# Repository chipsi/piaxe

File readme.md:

This Raspberry Pi mining HAT is based on the [BitAxe Ultra 1.3](https://github.com/skot/bitaxe
) (with BM1366) design.

Update: Miner is running stable 🥳

Changes to BitAxe Ultra
=======================

- powered by 12V and
- added TVS diode and fuses
- revised buck switching regulator circuit
- revised heatsink
- removed like DAC (only fixed 1.2V on PiAxe), current measurement, fan PWM controller, additional testpoints
- smallest components have 0805 size for easier manual assembly
- LM75 compatible temperature sensor under the heatsink

Installation
=============

- add to `/boot/config.txt`:
```
dtoverlay=pwm
```

- enable `serial` and `I2C` via `raspi-config`

If you want to use Influx and Grafana you need docker too:

```bash
$ curl -sSL https://get.docker.com | sh
```

Python:
```bash
# install pip3
$ sudo apt install python3-pip

# install libraries
$ for lib in pyserial rpi_hardware_pwm smbus influxdb-client pytz; do pip3 install $lib; done

# install i2c-tools
$ sudo apt install i2c-tools
```

Mining Client
=============

Stratum Mining Client:<br>
https://github.com/shufps/piaxe-miner

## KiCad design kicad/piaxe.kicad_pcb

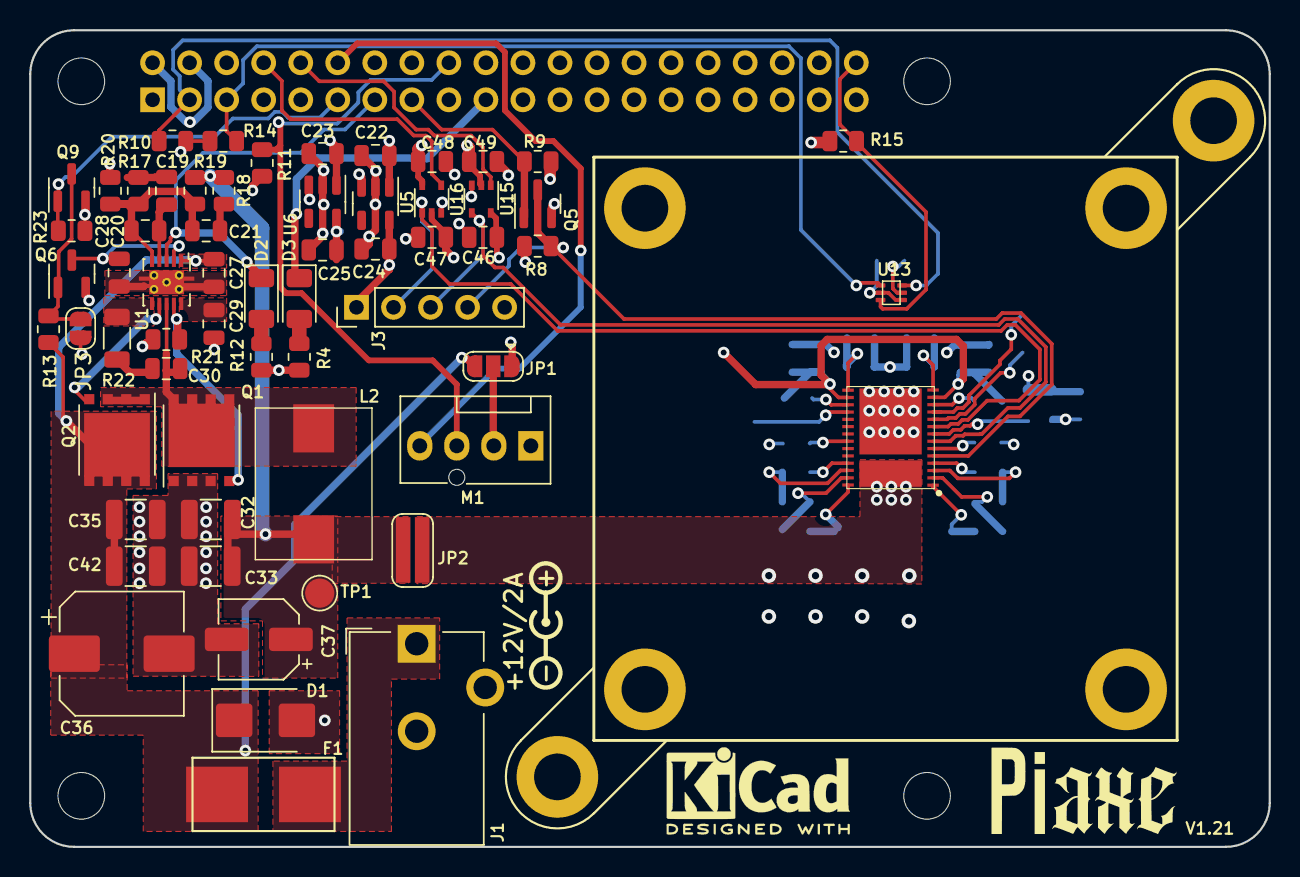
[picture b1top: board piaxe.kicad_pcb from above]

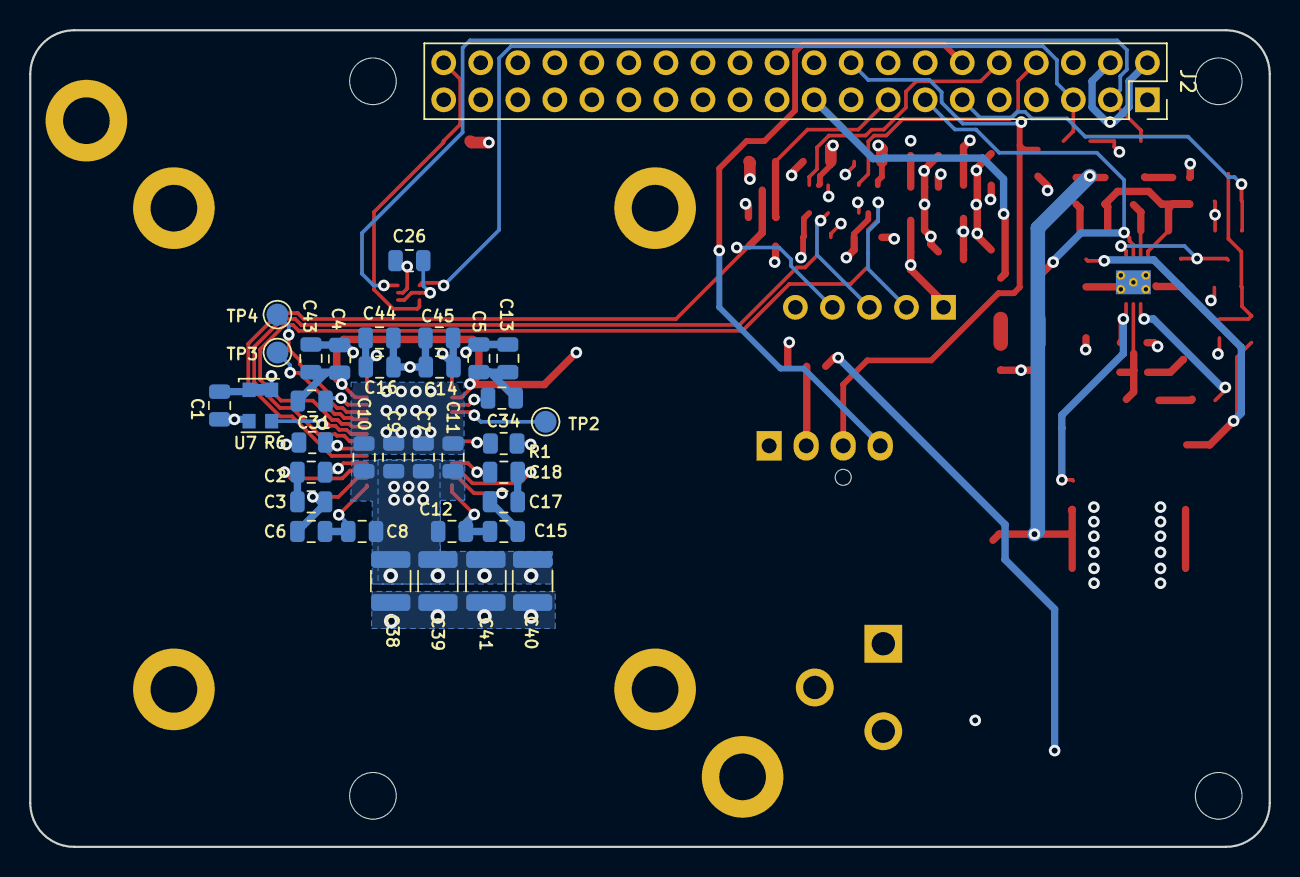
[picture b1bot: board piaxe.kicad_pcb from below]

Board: 4 copper layers, 85.0 x 56.0 mm, 103 parts (35 on the bottom side), 50 nets.

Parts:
C1, C7, C9, C13, C22, C23, C26, C30, C43, C44, C45, C46, C47, C48, C49: 100n; C_0805_2012Metric
C2, C3, C4, C5, C6, C8, C10, C11, C12, C14, C15, C16, C17, C18, C24, C25, C27, C31, C34: 1µ; C_0805_2012Metric
C19: 1.5n; C_0805_2012Metric
C20: 180p; C_0805_2012Metric
C21: 560p; C_0805_2012Metric
C28: 3.3n; C_0805_2012Metric
C29: 4.7µ/25V; C_0805_2012Metric
C32, C33, C40, C41: 47µ/6.3V; C_1210_3225Metric
C35: 1µ/25V; C_1210_3225Metric
C36: 330µ; CP_Elec_8x10
C37: 220µ; CP_Elec_5x5.8
C38, C39, C42: 10µ/25V; C_1210_3225Metric
D1: SMBJ12A; D_SMB
D2, D3: LED; LED_1206_3216Metric
F1: 2A; fuseholder_littlefuse_blok
H1, H2, H3, H4, H5, H6: MountingHole; MountingHole_3.2mm_M3_DIN965_Pad
J1: Barrel_Jack_Switch; BarrelJack_CUI_PJ-102AH_Horizontal
J2: Conn_02x20_Odd_Even; PinSocket_2x20_P2.54mm_Vertical
J3: Conn_01x05; PinHeader_1x05_P2.54mm_Vertical
JP1: SolderJumper_3_Open; SolderJumper-3_P1.3mm_Open_RoundedPad1.0x1.5mm
JP2: SolderJumper_2_Open; SolderJumper1.0x4.5
JP3: SolderJumper_2_Open; SolderJumper-2_P1.3mm_Open_RoundedPad1.0x1.5mm
L2: 170nH; IFLR-4031GC-01-8x10
M1: Fan_4pin; FanPinHeader_1x04_P2.54mm_Vertical
Q1, Q2: CSD17576Q5B; VSONP-8-1EP_5x6_P1.27mm
Q5, Q6, Q9: BSS138; SOT-23
R1, R6, R8, R9, R13, R15, R19, R20, R21, R23: 10k; R_0805_2012Metric
R4, R12: 560; R_0805_2012Metric
R10, R14: 1.5k; R_0805_2012Metric
R11: 2k2; R_0805_2012Metric
R17: 4.3k; R_0805_2012Metric
R18: 1.24k; R_0805_2012Metric
R22: 0; R_1206_3216Metric
TP1: +1V2; TestPoint_Pad_D2.0mm
TP2, TP3, TP4: TestPoint; TestPoint_Pad_D1.5mm
U1: TPS40305; VSON-10-1EP_3x3mm_P0.5mm_EP1.65x2.4mm_ThermalVias
U3: polarity
U5: MCP1824T-1802E; SOT-23-5
U6: MCP1824T-0802E; SOT-23-5
U7: 25MHz; Oscillator_SMD_EuroQuartz_XO32-4Pin_3.2x2.5mm
U13: TMP1075; TMP1075-DRL
U14: BM1366_mode1; BM1366
U15, U16: 2N7001TDCK; SOT-353_SC-70-5

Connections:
+0V8: C4.1, C5.1, C13.1, C25.1, C31.1, C34.2, C43.1, U6.5 (VOUT), U14.13 (VDDIO_08_0), U14.16 (VDDIO_08_1)
+1V2: C7.1, C8.2, C9.1, C10.1, C11.1, C12.1, C38.1, C39.1, C40.1, C41.1, JP2.2 (B), U14.29 (VDD)
+1V8: C1.1, C14.1, C16.1, C24.1, C44.1, C45.1, C46.1, C47.1, J3.1, R1.2, R8.2, U5.5 (VOUT), U7.1 (Standby), U7.4 (VDD), U14.14 (VDDIO_18_0), U14.15 (VDDIO_18_1), U15.5 (VCCA), U16.2 (VCCB)
+3V3: C26.1, C48.1, C49.1, J2.1, J2.17, R4.1, R9.2, R10.1, R11.1, R12.1, R14.1, R15.1, U13.5 (V+), U15.2 (VCCB), U16.5 (VCCA)
+5V: C22.1, C23.1, J2.2, J2.4, JP1.1 (A), U5.1 (VIN), U5.3 (EN), U6.1 (VIN), U6.3 (EN)
+12V: C27.1, C35.1, C36.1, C42.1, D1.1 (A1), F1.1, JP1.3 (B), Q2.3 (D), R13.2, U1.1 (VDD)
/BM1366/BI: R6.2, U14.6 (BI)
/BM1366/CI: J3.2, U14.9 (CI), U16.1 (B)
/BM1366/CLKI: U7.3 (Out), U14.8 (CLKI)
/BM1366/RO: J3.3, U14.7 (RO), U15.4 (A)
/BM1366/RST_N: J3.4, Q5.3 (D), R8.1, U14.5 (NRSTI)
/BM1366/TEMP_N: TP4.1, U14.11 (ADDR1)
/BM1366/TEMP_P: TP3.1, U14.10 (ADDR0)
/Pi/ALERT: J2.40, R15.2, U13.3 (ALERT)
/Pi/NRST: J2.15, Q5.1 (G), R9.1
/Pi/PGOOD: D2.1 (K), J2.13, U1.3 (PGOOD)
/Pi/PWM: J2.12, M1.4 (PWM)
/Pi/RXD: J2.10, U15.1 (B)
/Pi/SCL: J2.5, R14.2, U13.1 (SCL)
/Pi/SDA: J2.3, R10.2, U13.6 (SDA)
/Pi/SDN: J2.11, Q9.1 (G), R23.2
/Pi/TACHO: J2.18, M1.3 (Tacho), R11.2
/Pi/TXD: J2.8, U16.4 (A)
GND: C1.2, C2.1, C4.2, C5.2, C7.2, C9.2, C10.2, C11.2, C13.2, C14.2, C16.2, C18.2, C22.2, C23.2, C24.2, C25.2, C26.2, C27.2, C28.2, C29.2, C31.2, C32.2, C33.2, C34.1, C35.2, C36.2, C37.2, C38.2, C39.2, C40.2, C41.2, C42.2, C43.2, C44.2, C45.2, C46.2, C47.2, C48.2, C49.2, D1.2 (A2), J1.2, J1.3, J2.6, J2.9, J2.14, J2.20, J2.25, J2.30, J2.34, J2.39, J3.5, JP3.2 (B), M1.1 (-), Q1.1 (S), Q5.2 (S), Q6.2 (S), Q9.2 (S), R6.1, R20.1, R21.2, R23.1, U1.11 (GND), U5.2 (GND), U6.2 (GND), U7.2 (GND), U13.2 (GND), U13.4 (A0), U14.4 (VSS), U14.12 (PLL_VSS), U14.17 (VSS), U14.25 (VSS), U14.30 (GND), U15.3 (GND), U16.3 (GND)
unnamed: C19.2, R17.1
unnamed: C21.1, R18.2
unnamed: C30.1, R22.2
unnamed: D2.2 (A), R12.2
unnamed: D3.2 (A), R4.2
unnamed: D3.1 (K), J2.19
unnamed: F1.2, J1.1
unnamed: JP1.2 (C), M1.2 (+)
unnamed: C32.1, C33.1, C37.1, JP2.1 (A), L2.2, R18.1, R19.1, TP1.1
unnamed: JP3.1 (A), Q6.1 (G), Q9.3 (D), R13.1
unnamed: C30.2, L2.1, Q1.3 (D), Q2.1 (S), U1.8 (SW)
unnamed: Q1.2 (G), R21.1, U1.9 (LDRV/OC)
unnamed: Q2.2 (G), U1.7 (HDRV)
unnamed: C28.1, Q6.3 (D), U1.2 (EN/SS)
unnamed: R22.1, U1.6 (BOOT)
unnamed: C29.1, U1.10 (BP)
unnamed: C19.1, C20.1, U1.4 (COMP)
unnamed: C20.2, C21.2, R17.2, R19.2, R20.2, U1.5 (FB)
unnamed: TP2.1, U14.18 (PIN_MODE)
unnamed: R1.1, U14.22 (RI)
unnamed: C6.2, C8.1, U14.1 (VDD1_0)
unnamed: C12.2, C15.1, U14.28 (VDD1_1)
unnamed: C3.2, C6.1, U14.2 (VDD2_0)
unnamed: C15.2, C17.1, U14.27 (VDD2_1)
unnamed: C2.2, C3.1, U14.3 (VDD3_0)
unnamed: C17.2, C18.1, U14.26 (VDD3_1)

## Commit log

2023-10-21 added bitaxe variant for rasperry pi
2023-10-21 removed manufacturer files because layout is different now
2023-10-21 added missing schematic
2023-10-21 added back the two 1uF
2023-10-21 removed tantal and replaced with ceramic caps
2023-10-22 revised heat-sinking. Supports heatsinks with 40x40 size with holes 35x35, 32x32 and 33x33
2023-10-22 added gerbers and bom
2023-10-22 added 40x40 openscad and step model
2023-10-23 fixed zone-edgecut clearance, added 2nd gnd layer and stitched them together for copper balance
2023-10-23 removed useless snubber
2023-10-24 renamed project to piaxe
2023-10-26 added new 3d models
2023-11-06 fixed some order numbers, added initial python code for testing
2023-11-06 added c test code
2023-11-10 mining seems to work now
2023-11-10 removed unused module
2023-11-18 restructured a bit
2023-11-18 fixed paths to 3d models
2023-11-18 moved readme
2023-11-29 added solderjumper to enable the buck without Pi, changed LED values to 560R
2023-11-29 moved files
2023-11-29 fixed heatsink order number, updated BOM
2023-12-01 fixed net labeling to 1.2V
2023-12-21 initial commit before replacing power supply
2023-12-21 added mp8796 (wip)
2023-12-21 replaced caps
2023-12-23 updated gerber, bom
2023-12-24 added 3d models
2023-12-24 locked heatsink position
2023-12-28 push
2023-12-29 fixed bom for 2nd mosfet on buck
2024-01-04 gerbers and bom
2024-01-04 v0.02
2024-01-04 fixed bom
2024-01-19 switched pinheader on top to pinsocket on bottom
2024-01-30 Update LICENSE
